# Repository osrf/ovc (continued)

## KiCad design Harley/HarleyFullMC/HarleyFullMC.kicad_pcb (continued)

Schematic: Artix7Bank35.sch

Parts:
C131: 47u; C_0805; Voltage 10; Tolerance 20%
C132, C133: 4.7u; C_0402; Voltage 6.3; Tolerance 10%
C134, C135, C136, C137: 470n; C_0201; Voltage 6.3; Tolerance 10%
C138, C139, C140: 10n; C_0201; Voltage 6.3; Tolerance 10%
U1: xc7a100tcsg324pkg; BGA324C80P18X18_1500X1500X150; Voltage _; Tolerance _

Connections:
+1V0: U1.F8, U1.F10, U1.G7, U1.G9, U1.G11, U1.H8, U1.J7, U1.J11, U1.K8, U1.L7, U1.L11, U1.M8, U1.M10, U1.N7, U1.N9, U1.N11; also elsewhere on the board
+1V8: U1.F12, U1.H12, U1.K12, U1.M12; also elsewhere on the board
+2V5: U1.A17, U1.C13, U1.D16, U1.G15, U1.H18, U1.K4, U1.K14, U1.L17, U1.N3, U1.N13, U1.P6, U1.P8, U1.P11, U1.P12, U1.P13, U1.P16, U1.R9, U1.T2, U1.T12, U1.U5, U1.U15, U1.V8, U1.V18; also elsewhere on the board
+3V3: U1.B10; also elsewhere on the board
/Sheet56A15EBD/GND_ADC: U1.H9, U1.J9, U1.K10; also elsewhere on the board
Artix_FX3_CLK: U1.P3; also elsewhere on the board
CAM_CLK_IN+: U1.B13; also elsewhere on the board
CAM_CLK_IN-: U1.B14; also elsewhere on the board
CAM_CLK_OUT+: U1.F15; also elsewhere on the board
CAM_CLK_OUT-: U1.F16; also elsewhere on the board
CAM_CLK_PLL: U1.C10; also elsewhere on the board
CAM_DOUT0+: U1.A11; also elsewhere on the board
CAM_DOUT0-: U1.B11; also elsewhere on the board
CAM_DOUT1+: U1.A14; also elsewhere on the board
CAM_DOUT1-: U1.A13; also elsewhere on the board
CAM_DOUT2+: U1.A16; also elsewhere on the board
CAM_DOUT2-: U1.A15; also elsewhere on the board
CAM_DOUT3+: U1.B17; also elsewhere on the board
CAM_DOUT3-: U1.B16; also elsewhere on the board
CAM_RST#: U1.B9; also elsewhere on the board
CAM_SS#: U1.A8; also elsewhere on the board
CAM_SYNC+: U1.B18; also elsewhere on the board
CAM_SYNC-: U1.A18; also elsewhere on the board
CAM_monitor0: U1.A10; also elsewhere on the board
CAM_trigger0: U1.D10; also elsewhere on the board
CAM_trigger1: U1.D9; also elsewhere on the board
DDR_A0: U1.G2; also elsewhere on the board
DDR_A1: U1.H5; also elsewhere on the board
DDR_A2: U1.G3; also elsewhere on the board
DDR_A3: U1.H2; also elsewhere on the board
DDR_A4: U1.J4; also elsewhere on the board
DDR_A5: U1.J2; also elsewhere on the board
DDR_A6: U1.G6; also elsewhere on the board
DDR_A7: U1.K1; also elsewhere on the board
DDR_A8: U1.H6; also elsewhere on the board
DDR_A9: U1.J3; also elsewhere on the board
DDR_A10: U1.F6; also elsewhere on the board
DDR_A11: U1.H4; also elsewhere on the board
DDR_A12: U1.G4; also elsewhere on the board
DDR_A13: U1.K2; also elsewhere on the board
DDR_BA0: U1.E1; also elsewhere on the board
DDR_BA1: U1.G1; also elsewhere on the board
DDR_BA2: U1.F1; also elsewhere on the board
DDR_CAS#: U1.C1; also elsewhere on the board
DDR_CKE: U1.H1; also elsewhere on the board
DDR_CLK+: U1.F4; also elsewhere on the board
DDR_CLK-: U1.F3; also elsewhere on the board
DDR_DQL0: U1.B7; also elsewhere on the board
DDR_DQL1: U1.D8; also elsewhere on the board
DDR_DQL2: U1.C7; also elsewhere on the board
DDR_DQL3: U1.B6; also elsewhere on the board
DDR_DQL4: U1.E5; also elsewhere on the board
DDR_DQL5: U1.D7; also elsewhere on the board
DDR_DQL6: U1.E6; also elsewhere on the board
DDR_DQL7: U1.E7; also elsewhere on the board
DDR_DQSL+: U1.A6; also elsewhere on the board
DDR_DQSL-: U1.A5; also elsewhere on the board
DDR_DQSU+: U1.B1; also elsewhere on the board
DDR_DQSU-: U1.A1; also elsewhere on the board
DDR_DQU0: U1.B2; also elsewhere on the board
DDR_DQU1: U1.D4; also elsewhere on the board
DDR_DQU2: U1.B3; also elsewhere on the board
DDR_DQU3: U1.D5; also elsewhere on the board
DDR_DQU4: U1.B4; also elsewhere on the board
DDR_DQU5: U1.C4; also elsewhere on the board
DDR_DQU6: U1.A3; also elsewhere on the board
DDR_DQU7: U1.A4; also elsewhere on the board
DDR_ODT: U1.E2; also elsewhere on the board
DDR_RAS#: U1.C2; also elsewhere on the board
DDR_RST#: U1.J5; also elsewhere on the board
DDR_VDD: C131.1, C132.1, C133.1, C134.1, C135.1, C136.1, C137.1, C138.1, C139.1, C140.1, U1.A7, U1.C3, U1.D6, U1.F2, U1.G5, U1.J1; also elsewhere on the board
DDR_WE#: U1.D2; also elsewhere on the board
FPGADebug1: U1.C16; also elsewhere on the board
FPGADebug2: U1.F14; also elsewhere on the board
FPGA_CLK: U1.N5; also elsewhere on the board
FPGA_JTAG_TCK: U1.E10; also elsewhere on the board
FPGA_JTAG_TDI: U1.E11; also elsewhere on the board
FPGA_JTAG_TDO: U1.E13; also elsewhere on the board
FPGA_JTAG_TMS: U1.E12; also elsewhere on the board
FPGA_LED: U1.C17; also elsewhere on the board
FPGA_SS_CCLK: U1.E9; also elsewhere on the board
FPGA_SS_DIN: U1.K18; also elsewhere on the board
FPGA_SS_DONE: U1.P10; also elsewhere on the board
FPGA_SS_DOUT: U1.T16; also elsewhere on the board
FPGA_SS_INIT_B: U1.P7; also elsewhere on the board
FPGA_SS_PROGRAM_B: U1.P9; also elsewhere on the board
FX3_A0: U1.T9; also elsewhere on the board
FX3_A1: U1.R11; also elsewhere on the board
FX3_DQ0: U1.V7; also elsewhere on the board
FX3_DQ1: U1.R3; also elsewhere on the board
FX3_DQ2: U1.R2; also elsewhere on the board
FX3_DQ3: U1.V4; also elsewhere on the board
FX3_DQ4: U1.T4; also elsewhere on the board
FX3_DQ5: U1.T3; also elsewhere on the board
FX3_DQ6: U1.V9; also elsewhere on the board
FX3_DQ7: U1.U6; also elsewhere on the board
FX3_DQ8: U1.V10; also elsewhere on the board
FX3_DQ9: U1.V11; also elsewhere on the board
FX3_DQ10: U1.U11; also elsewhere on the board
FX3_DQ11: U1.U13; also elsewhere on the board
FX3_DQ12: U1.V12; also elsewhere on the board
FX3_DQ13: U1.V14; also elsewhere on the board
FX3_DQ14: U1.T10; also elsewhere on the board
FX3_DQ15: U1.T5; also elsewhere on the board
FX3_DQ16: U1.U16; also elsewhere on the board
FX3_DQ17: U1.U12; also elsewhere on the board
FX3_DQ18: U1.V17; also elsewhere on the board
FX3_DQ19: U1.T14; also elsewhere on the board
FX3_DQ20: U1.V16; also elsewhere on the board
FX3_DQ21: U1.P14; also elsewhere on the board
FX3_DQ22: U1.R12; also elsewhere on the board
FX3_DQ23: U1.T11; also elsewhere on the board
FX3_DQ24: U1.P5; also elsewhere on the board
FX3_DQ25: U1.T13; also elsewhere on the board
FX3_DQ26: U1.R8; also elsewhere on the board
FX3_DQ27: U1.L14; also elsewhere on the board
FX3_DQ28: U1.U4; also elsewhere on the board
FX3_DQ29: U1.P18; also elsewhere on the board
FX3_DQ30: U1.V1; also elsewhere on the board
FX3_DQ31: U1.R16; also elsewhere on the board
FX3_FLAGA: U1.V6; also elsewhere on the board
FX3_FLAGB: U1.U9; also elsewhere on the board
FX3_FLAGC: U1.T15; also elsewhere on the board
FX3_FLAGD: U1.T8; also elsewhere on the board
FX3_PKT_END#: U1.R5; also elsewhere on the board
FX3_SLCS#: U1.U14; also elsewhere on the board
FX3_SLOE#: U1.R10; also elsewhere on the board
FX3_SLRD#: U1.R6; also elsewhere on the board
FX3_SLWR#: U1.V15; also elsewhere on the board
GND: C131.2, C132.2, C133.2, C134.2, C135.2, C136.2, C137.2, C138.2, C139.2, C140.2, U1.A2, U1.A12, U1.B5, U1.B15, U1.C8, U1.C18, U1.D1, U1.D11, U1.E4, U1.E8, U1.E14, U1.F7, U1.F9, U1.F11, U1.F17, U1.G8, U1.G10, U1.G12, U1.H3, U1.H7, U1.H11, U1.H13, U1.J6, U1.J8, U1.J10, U1.J12, U1.J16, U1.K7, U1.K9, U1.K11, U1.L2, U1.L8, U1.L9, U1.L10, U1.L12, U1.M5, U1.M7, U1.M9, U1.M11, U1.M15, U1.N8, U1.N10, U1.N12, U1.N18, U1.P1, U1.R4, U1.R14, U1.T7, U1.T17, U1.U10, U1.V3, U1.V13; also elsewhere on the board
IMU_SS#: U1.C11; also elsewhere on the board
unnamed 164: U1.H10; also elsewhere on the board
P_LVDS1+: U1.E18; also elsewhere on the board
P_LVDS1-: U1.D18; also elsewhere on the board
P_LVDS2+: U1.G18; also elsewhere on the board
P_LVDS2-: U1.F18; also elsewhere on the board
P_LVDS3+: U1.J17; also elsewhere on the board
P_LVDS3-: U1.J18; also elsewhere on the board
P_LVDS4+: U1.H16; also elsewhere on the board
P_LVDS4-: U1.G16; also elsewhere on the board
P_LVDS5+: U1.H14; also elsewhere on the board
P_LVDS5-: U1.G14; also elsewhere on the board
P_LVDS6+: U1.M18; also elsewhere on the board
P_LVDS6-: U1.L18; also elsewhere on the board
P_LVDS7+: U1.L15; also elsewhere on the board
P_LVDS7-: U1.L16; also elsewhere on the board
P_LVDS8+: U1.N15; also elsewhere on the board
P_LVDS8-: U1.N16; also elsewhere on the board
P_LVDS9+: U1.T18; also elsewhere on the board
P_LVDS9-: U1.R18; also elsewhere on the board
P_LVDS10+: U1.U17; also elsewhere on the board
P_LVDS10-: U1.U18; also elsewhere on the board
P_LVDS11+: U1.D17; also elsewhere on the board
P_LVDS11-: U1.E17; also elsewhere on the board
P_LVDS12+: U1.R17; also elsewhere on the board
P_LVDS12-: U1.P17; also elsewhere on the board
P_LVDS13+: U1.R15; also elsewhere on the board
P_LVDS13-: U1.P15; also elsewhere on the board
P_LVDS14+: U1.M13; also elsewhere on the board
P_LVDS14-: U1.L13; also elsewhere on the board
SPI_MISO: U1.A9; also elsewhere on the board
SPI_MOSI: U1.C9; also elsewhere on the board
SPI_SCK: U1.B8; also elsewhere on the board

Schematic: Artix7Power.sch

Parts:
C103: 330u; C_1210; Voltage 4; Tolerance 20%
C104: 100u; C_1206; Voltage 6.3; Tolerance 20%
C105: 47u; C_0805; Voltage 10; Tolerance 20%
C106, C107, C109, C110, C113, C127, C129: 4.7u; C_0402; Voltage 6.3; Tolerance 10%
C111, C112, C115, C117, C119, C120, C121, C122, C123, C124, C130, C161: 470n; C_0201; Voltage 6.3; Tolerance 10%
U1: xc7a100tcsg324pkg; BGA324C80P18X18_1500X1500X150; Voltage _; Tolerance _

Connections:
+1V0: C103.1, C104.1, C107.1, C110.1, C111.1, C113.1, C120.1, C121.1, C122.1, C123.1, C124.1, C127.1, C129.1, C130.1, C161.1, U1.F8, U1.F10, U1.G7, U1.G9, U1.G11, U1.H8, U1.J7, U1.J11, U1.K8, U1.L7, U1.L11, U1.M8, U1.M10, U1.N7, U1.N9, U1.N11; also elsewhere on the board
+1V8: C105.1, C106.1, C109.1, C112.1, C115.1, C117.1, C119.1, U1.F12, U1.H12, U1.K12, U1.M12; also elsewhere on the board
+2V5: U1.A17, U1.C13, U1.D16, U1.G15, U1.H18, U1.K4, U1.K14, U1.L17, U1.N3, U1.N13, U1.P6, U1.P8, U1.P11, U1.P12, U1.P13, U1.P16, U1.R9, U1.T2, U1.T12, U1.U5, U1.U15, U1.V8, U1.V18; also elsewhere on the board
+3V3: U1.B10; also elsewhere on the board
/Sheet56A15EBD/GND_ADC: U1.H9, U1.J9, U1.K10; also elsewhere on the board
Artix_FX3_CLK: U1.P3; also elsewhere on the board
CAM_CLK_IN+: U1.B13; also elsewhere on the board
CAM_CLK_IN-: U1.B14; also elsewhere on the board
CAM_CLK_OUT+: U1.F15; also elsewhere on the board
CAM_CLK_OUT-: U1.F16; also elsewhere on the board
CAM_CLK_PLL: U1.C10; also elsewhere on the board
CAM_DOUT0+: U1.A11; also elsewhere on the board
CAM_DOUT0-: U1.B11; also elsewhere on the board
CAM_DOUT1+: U1.A14; also elsewhere on the board
CAM_DOUT1-: U1.A13; also elsewhere on the board
CAM_DOUT2+: U1.A16; also elsewhere on the board
CAM_DOUT2-: U1.A15; also elsewhere on the board
CAM_DOUT3+: U1.B17; also elsewhere on the board
CAM_DOUT3-: U1.B16; also elsewhere on the board
CAM_RST#: U1.B9; also elsewhere on the board
CAM_SS#: U1.A8; also elsewhere on the board
CAM_SYNC+: U1.B18; also elsewhere on the board
CAM_SYNC-: U1.A18; also elsewhere on the board
CAM_monitor0: U1.A10; also elsewhere on the board
CAM_trigger0: U1.D10; also elsewhere on the board
CAM_trigger1: U1.D9; also elsewhere on the board
DDR_A0: U1.G2; also elsewhere on the board
DDR_A1: U1.H5; also elsewhere on the board
DDR_A2: U1.G3; also elsewhere on the board
DDR_A3: U1.H2; also elsewhere on the board
DDR_A4: U1.J4; also elsewhere on the board
DDR_A5: U1.J2; also elsewhere on the board
DDR_A6: U1.G6; also elsewhere on the board
DDR_A7: U1.K1; also elsewhere on the board
DDR_A8: U1.H6; also elsewhere on the board
DDR_A9: U1.J3; also elsewhere on the board
DDR_A10: U1.F6; also elsewhere on the board
DDR_A11: U1.H4; also elsewhere on the board
DDR_A12: U1.G4; also elsewhere on the board
DDR_A13: U1.K2; also elsewhere on the board
DDR_BA0: U1.E1; also elsewhere on the board
DDR_BA1: U1.G1; also elsewhere on the board
DDR_BA2: U1.F1; also elsewhere on the board
DDR_CAS#: U1.C1; also elsewhere on the board
DDR_CKE: U1.H1; also elsewhere on the board
DDR_CLK+: U1.F4; also elsewhere on the board
DDR_CLK-: U1.F3; also elsewhere on the board
DDR_DQL0: U1.B7; also elsewhere on the board
DDR_DQL1: U1.D8; also elsewhere on the board
DDR_DQL2: U1.C7; also elsewhere on the board
DDR_DQL3: U1.B6; also elsewhere on the board
DDR_DQL4: U1.E5; also elsewhere on the board
DDR_DQL5: U1.D7; also elsewhere on the board
DDR_DQL6: U1.E6; also elsewhere on the board
DDR_DQL7: U1.E7; also elsewhere on the board
DDR_DQSL+: U1.A6; also elsewhere on the board
DDR_DQSL-: U1.A5; also elsewhere on the board
DDR_DQSU+: U1.B1; also elsewhere on the board
DDR_DQSU-: U1.A1; also elsewhere on the board
DDR_DQU0: U1.B2; also elsewhere on the board
DDR_DQU1: U1.D4; also elsewhere on the board
DDR_DQU2: U1.B3; also elsewhere on the board
DDR_DQU3: U1.D5; also elsewhere on the board
DDR_DQU4: U1.B4; also elsewhere on the board
DDR_DQU5: U1.C4; also elsewhere on the board
DDR_DQU6: U1.A3; also elsewhere on the board
DDR_DQU7: U1.A4; also elsewhere on the board
DDR_ODT: U1.E2; also elsewhere on the board
DDR_RAS#: U1.C2; also elsewhere on the board
DDR_RST#: U1.J5; also elsewhere on the board
DDR_VDD: U1.A7, U1.C3, U1.D6, U1.F2, U1.G5, U1.J1; also elsewhere on the board
DDR_WE#: U1.D2; also elsewhere on the board
FPGADebug1: U1.C16; also elsewhere on the board
FPGADebug2: U1.F14; also elsewhere on the board
FPGA_CLK: U1.N5; also elsewhere on the board
FPGA_JTAG_TCK: U1.E10; also elsewhere on the board
FPGA_JTAG_TDI: U1.E11; also elsewhere on the board
FPGA_JTAG_TDO: U1.E13; also elsewhere on the board
FPGA_JTAG_TMS: U1.E12; also elsewhere on the board
FPGA_LED: U1.C17; also elsewhere on the board
FPGA_SS_CCLK: U1.E9; also elsewhere on the board
FPGA_SS_DIN: U1.K18; also elsewhere on the board
FPGA_SS_DONE: U1.P10; also elsewhere on the board
FPGA_SS_DOUT: U1.T16; also elsewhere on the board
FPGA_SS_INIT_B: U1.P7; also elsewhere on the board
FPGA_SS_PROGRAM_B: U1.P9; also elsewhere on the board
FX3_A0: U1.T9; also elsewhere on the board
FX3_A1: U1.R11; also elsewhere on the board
FX3_DQ0: U1.V7; also elsewhere on the board
FX3_DQ1: U1.R3; also elsewhere on the board
FX3_DQ2: U1.R2; also elsewhere on the board
FX3_DQ3: U1.V4; also elsewhere on the board
FX3_DQ4: U1.T4; also elsewhere on the board
FX3_DQ5: U1.T3; also elsewhere on the board
FX3_DQ6: U1.V9; also elsewhere on the board
FX3_DQ7: U1.U6; also elsewhere on the board
FX3_DQ8: U1.V10; also elsewhere on the board
FX3_DQ9: U1.V11; also elsewhere on the board
FX3_DQ10: U1.U11; also elsewhere on the board
FX3_DQ11: U1.U13; also elsewhere on the board
FX3_DQ12: U1.V12; also elsewhere on the board
FX3_DQ13: U1.V14; also elsewhere on the board
FX3_DQ14: U1.T10; also elsewhere on the board
FX3_DQ15: U1.T5; also elsewhere on the board
FX3_DQ16: U1.U16; also elsewhere on the board
FX3_DQ17: U1.U12; also elsewhere on the board
FX3_DQ18: U1.V17; also elsewhere on the board
FX3_DQ19: U1.T14; also elsewhere on the board
FX3_DQ20: U1.V16; also elsewhere on the board
FX3_DQ21: U1.P14; also elsewhere on the board
FX3_DQ22: U1.R12; also elsewhere on the board
FX3_DQ23: U1.T11; also elsewhere on the board
FX3_DQ24: U1.P5; also elsewhere on the board
FX3_DQ25: U1.T13; also elsewhere on the board
FX3_DQ26: U1.R8; also elsewhere on the board
FX3_DQ27: U1.L14; also elsewhere on the board
FX3_DQ28: U1.U4; also elsewhere on the board
FX3_DQ29: U1.P18; also elsewhere on the board
FX3_DQ30: U1.V1; also elsewhere on the board
FX3_DQ31: U1.R16; also elsewhere on the board
FX3_FLAGA: U1.V6; also elsewhere on the board
FX3_FLAGB: U1.U9; also elsewhere on the board
FX3_FLAGC: U1.T15; also elsewhere on the board
FX3_FLAGD: U1.T8; also elsewhere on the board
FX3_PKT_END#: U1.R5; also elsewhere on the board
FX3_SLCS#: U1.U14; also elsewhere on the board
FX3_SLOE#: U1.R10; also elsewhere on the board
FX3_SLRD#: U1.R6; also elsewhere on the board
FX3_SLWR#: U1.V15; also elsewhere on the board
GND: C103.2, C104.2, C105.2, C106.2, C107.2, C109.2, C110.2, C111.2, C112.2, C113.2, C115.2, C117.2, C119.2, C120.2, C121.2, C122.2, C123.2, C124.2, C127.2, C129.2, C130.2, C161.2, U1.A2, U1.A12, U1.B5, U1.B15, U1.C8, U1.C18, U1.D1, U1.D11, U1.E4, U1.E8, U1.E14, U1.F7, U1.F9, U1.F11, U1.F17, U1.G8, U1.G10, U1.G12, U1.H3, U1.H7, U1.H11, U1.H13, U1.J6, U1.J8, U1.J10, U1.J12, U1.J16, U1.K7, U1.K9, U1.K11, U1.L2, U1.L8, U1.L9, U1.L10, U1.L12, U1.M5, U1.M7, U1.M9, U1.M11, U1.M15, U1.N8, U1.N10, U1.N12, U1.N18, U1.P1, U1.R4, U1.R14, U1.T7, U1.T17, U1.U10, U1.V3, U1.V13; also elsewhere on the board
IMU_SS#: U1.C11; also elsewhere on the board
unnamed 164: U1.H10; also elsewhere on the board
P_LVDS1+: U1.E18; also elsewhere on the board
P_LVDS1-: U1.D18; also elsewhere on the board
P_LVDS2+: U1.G18; also elsewhere on the board
P_LVDS2-: U1.F18; also elsewhere on the board
P_LVDS3+: U1.J17; also elsewhere on the board
P_LVDS3-: U1.J18; also elsewhere on the board
P_LVDS4+: U1.H16; also elsewhere on the board
P_LVDS4-: U1.G16; also elsewhere on the board
P_LVDS5+: U1.H14; also elsewhere on the board
P_LVDS5-: U1.G14; also elsewhere on the board
P_LVDS6+: U1.M18; also elsewhere on the board
P_LVDS6-: U1.L18; also elsewhere on the board
P_LVDS7+: U1.L15; also elsewhere on the board
P_LVDS7-: U1.L16; also elsewhere on the board
P_LVDS8+: U1.N15; also elsewhere on the board
P_LVDS8-: U1.N16; also elsewhere on the board
P_LVDS9+: U1.T18; also elsewhere on the board
P_LVDS9-: U1.R18; also elsewhere on the board
P_LVDS10+: U1.U17; also elsewhere on the board
P_LVDS10-: U1.U18; also elsewhere on the board
P_LVDS11+: U1.D17; also elsewhere on the board
P_LVDS11-: U1.E17; also elsewhere on the board
P_LVDS12+: U1.R17; also elsewhere on the board
P_LVDS12-: U1.P17; also elsewhere on the board
P_LVDS13+: U1.R15; also elsewhere on the board
P_LVDS13-: U1.P15; also elsewhere on the board
P_LVDS14+: U1.M13; also elsewhere on the board
P_LVDS14-: U1.L13; also elsewhere on the board
SPI_MISO: U1.A9; also elsewhere on the board
SPI_MOSI: U1.C9; also elsewhere on the board
SPI_SCK: U1.B8; also elsewhere on the board

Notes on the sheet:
VCCINT
VCCBRAM
VCCAUX
Additional Decoupling for XC7A100T

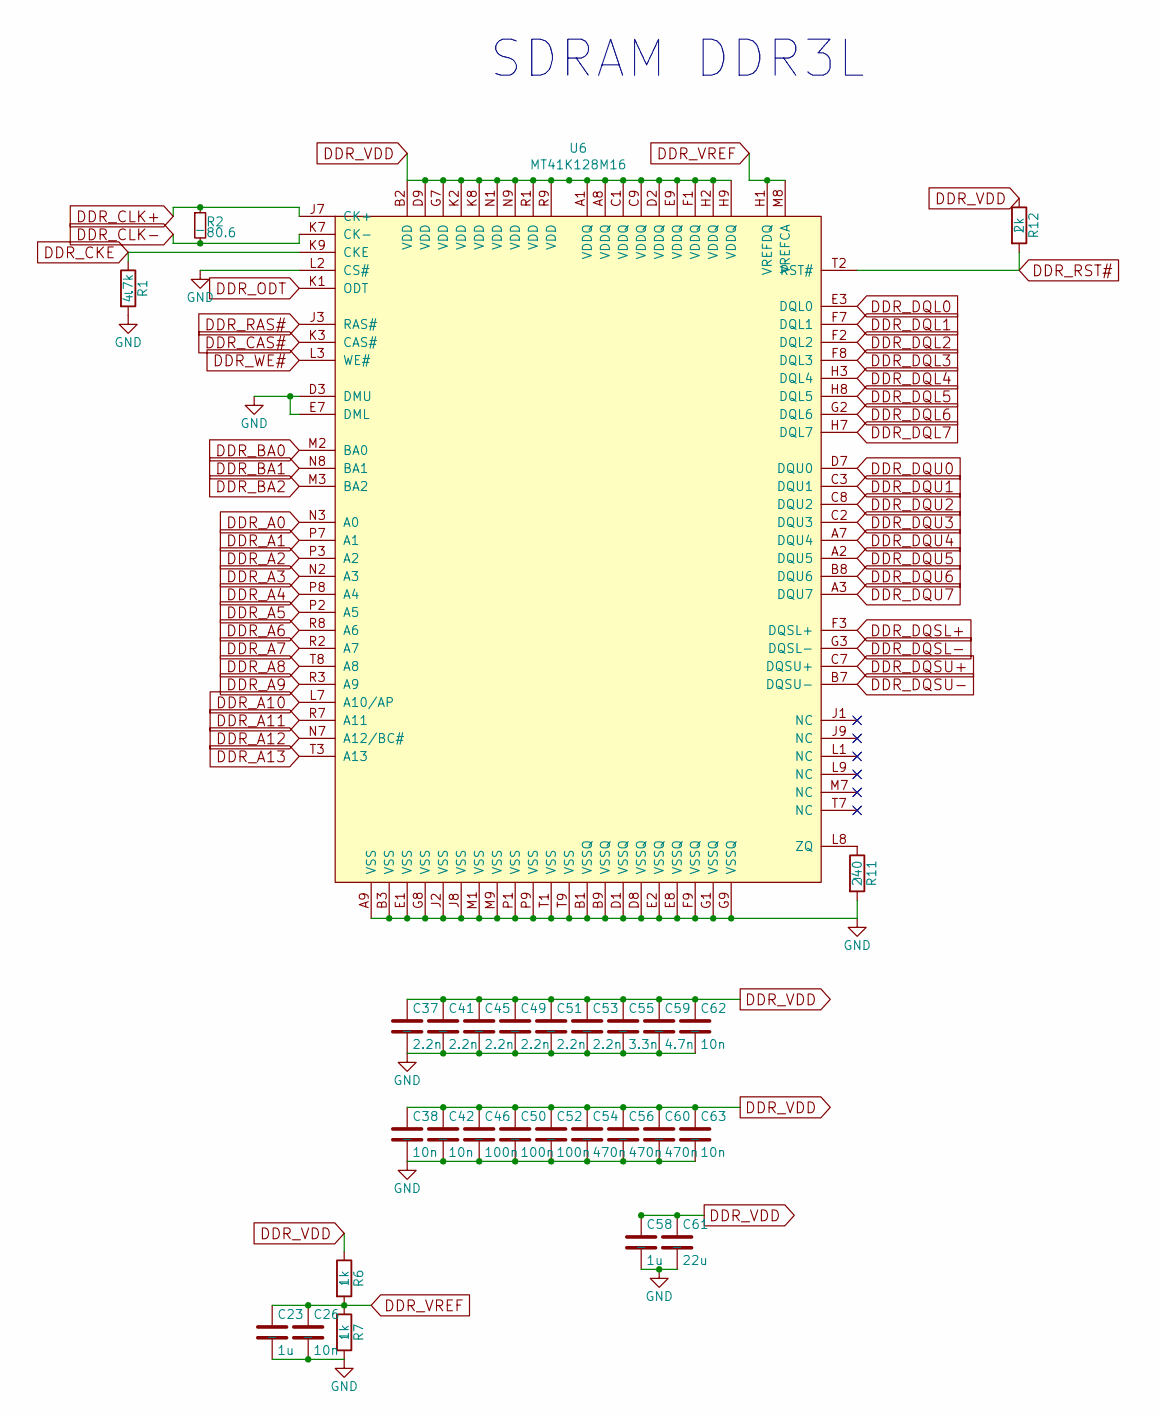
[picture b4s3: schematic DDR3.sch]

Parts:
C23, C58: 1u; C_0201; Voltage 6.3; Tolerance 20%
C26, C38, C42, C62, C63: 10n; C_0201; Voltage 10; Tolerance 10%
C37, C41, C45, C49, C51, C53: 2.2n; C_0201; Voltage 25; Tolerance 10%
C46, C50, C52: 100n; C_0201; Voltage 6.3; Tolerance 10%
C54, C56, C60: 470n; C_0201; Voltage 6.3; Tolerance 10%
C55: 3.3n; C_0201; Voltage 25; Tolerance 10%
C59: 4.7n; C_0201; Voltage 16; Tolerance 10%
C61: 22u; C_0805; Voltage 6.3; Tolerance 10%
R1: 4.7k; C_0201; Voltage _; Tolerance 1%
R2: 80.6; C_0201; Voltage _; Tolerance 1%
R6, R7: 1k; C_0201; Voltage _; Tolerance 1%
R11: 240; C_0201; Voltage _; Tolerance 1%
R12: 2k; C_0201; Voltage _; Tolerance 1%
U6: MT41K128M16; WBGA96C80P6X16_80X1400X110; Voltage _; Tolerance _

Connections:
DDR_A0: U6.N3 (A0); also elsewhere on the board
DDR_A1: U6.P7 (A1); also elsewhere on the board
DDR_A2: U6.P3 (A2); also elsewhere on the board
DDR_A3: U6.N2 (A3); also elsewhere on the board
DDR_A4: U6.P8 (A4); also elsewhere on the board
DDR_A5: U6.P2 (A5); also elsewhere on the board
DDR_A6: U6.R8 (A6); also elsewhere on the board
DDR_A7: U6.R2 (A7); also elsewhere on the board
DDR_A8: U6.T8 (A8); also elsewhere on the board
DDR_A9: U6.R3 (A9); also elsewhere on the board
DDR_A10: U6.L7 (A10/AP); also elsewhere on the board
DDR_A11: U6.R7 (A11); also elsewhere on the board
DDR_A12: U6.N7 (A12/BC#); also elsewhere on the board
DDR_A13: U6.T3 (A13); also elsewhere on the board
DDR_BA0: U6.M2 (BA0); also elsewhere on the board
DDR_BA1: U6.N8 (BA1); also elsewhere on the board
DDR_BA2: U6.M3 (BA2); also elsewhere on the board
DDR_CAS#: U6.K3 (CAS#); also elsewhere on the board
DDR_CKE: R1.1, U6.K9 (CKE); also elsewhere on the board
DDR_CLK+: R2.1, U6.J7 (CK+); also elsewhere on the board
DDR_CLK-: R2.2, U6.K7 (CK-); also elsewhere on the board
DDR_DQL0: U6.E3 (DQL0); also elsewhere on the board
DDR_DQL1: U6.F7 (DQL1); also elsewhere on the board
DDR_DQL2: U6.F2 (DQL2); also elsewhere on the board
DDR_DQL3: U6.F8 (DQL3); also elsewhere on the board
DDR_DQL4: U6.H3 (DQL4); also elsewhere on the board
DDR_DQL5: U6.H8 (DQL5); also elsewhere on the board
DDR_DQL6: U6.G2 (DQL6); also elsewhere on the board
DDR_DQL7: U6.H7 (DQL7); also elsewhere on the board
DDR_DQSL+: U6.F3 (DQSL+); also elsewhere on the board
DDR_DQSL-: U6.G3 (DQSL-); also elsewhere on the board
DDR_DQSU+: U6.C7 (DQSU+); also elsewhere on the board
DDR_DQSU-: U6.B7 (DQSU-); also elsewhere on the board
DDR_DQU0: U6.D7 (DQU0); also elsewhere on the board
DDR_DQU1: U6.C3 (DQU1); also elsewhere on the board
DDR_DQU2: U6.C8 (DQU2); also elsewhere on the board
DDR_DQU3: U6.C2 (DQU3); also elsewhere on the board
DDR_DQU4: U6.A7 (DQU4); also elsewhere on the board
DDR_DQU5: U6.A2 (DQU5); also elsewhere on the board
DDR_DQU6: U6.B8 (DQU6); also elsewhere on the board
DDR_DQU7: U6.A3 (DQU7); also elsewhere on the board
DDR_ODT: U6.K1 (ODT); also elsewhere on the board
DDR_RAS#: U6.J3 (RAS#); also elsewhere on the board
DDR_RST#: R12.2, U6.T2 (RST#); also elsewhere on the board
DDR_VDD: C37.1, C38.1, C41.1, C42.1, C45.1, C46.1, C49.1, C50.1, C51.1, C52.1, C53.1, C54.1, C55.1, C56.1, C58.1, C59.1, C60.1, C61.1, C62.1, C63.1, R6.1, R12.1, U6.A1 (VDDQ), U6.A8 (VDDQ), U6.B2 (VDD), U6.C1 (VDDQ), U6.C9 (VDDQ), U6.D2 (VDDQ), U6.D9 (VDD), U6.E9 (VDDQ), U6.F1 (VDDQ), U6.G7 (VDD), U6.H2 (VDDQ), U6.H9 (VDDQ), U6.K2 (VDD), U6.K8 (VDD), U6.N1 (VDD), U6.N9 (VDD), U6.R1 (VDD), U6.R9 (VDD); also elsewhere on the board
DDR_VREF: C23.1, C26.1, R6.2, R7.1, U6.H1 (VREFDQ), U6.M8 (VREFCA)
DDR_WE#: U6.L3 (WE#); also elsewhere on the board
GND: C23.2, C26.2, C37.2, C38.2, C41.2, C42.2, C45.2, C46.2, C49.2, C50.2, C51.2, C52.2, C53.2, C54.2, C55.2, C56.2, C58.2, C59.2, C60.2, C61.2, C62.2, C63.2, R1.2, R7.2, R11.2, U6.A9 (VSS), U6.B1 (VSSQ), U6.B3 (VSS), U6.B9 (VSSQ), U6.D1 (VSSQ), U6.D3 (DMU), U6.D8 (VSSQ), U6.E1 (VSS), U6.E2 (VSSQ), U6.E7 (DML), U6.E8 (VSSQ), U6.F9 (VSSQ), U6.G1 (VSSQ), U6.G8 (VSS), U6.G9 (VSSQ), U6.J2 (VSS), U6.J8 (VSS), U6.L2 (CS#), U6.M1 (VSS), U6.M9 (VSS), U6.P1 (VSS), U6.P9 (VSS), U6.T1 (VSS), U6.T9 (VSS); also elsewhere on the board
unnamed: R11.1, U6.L8 (ZQ)

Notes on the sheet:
SDRAM DDR3L

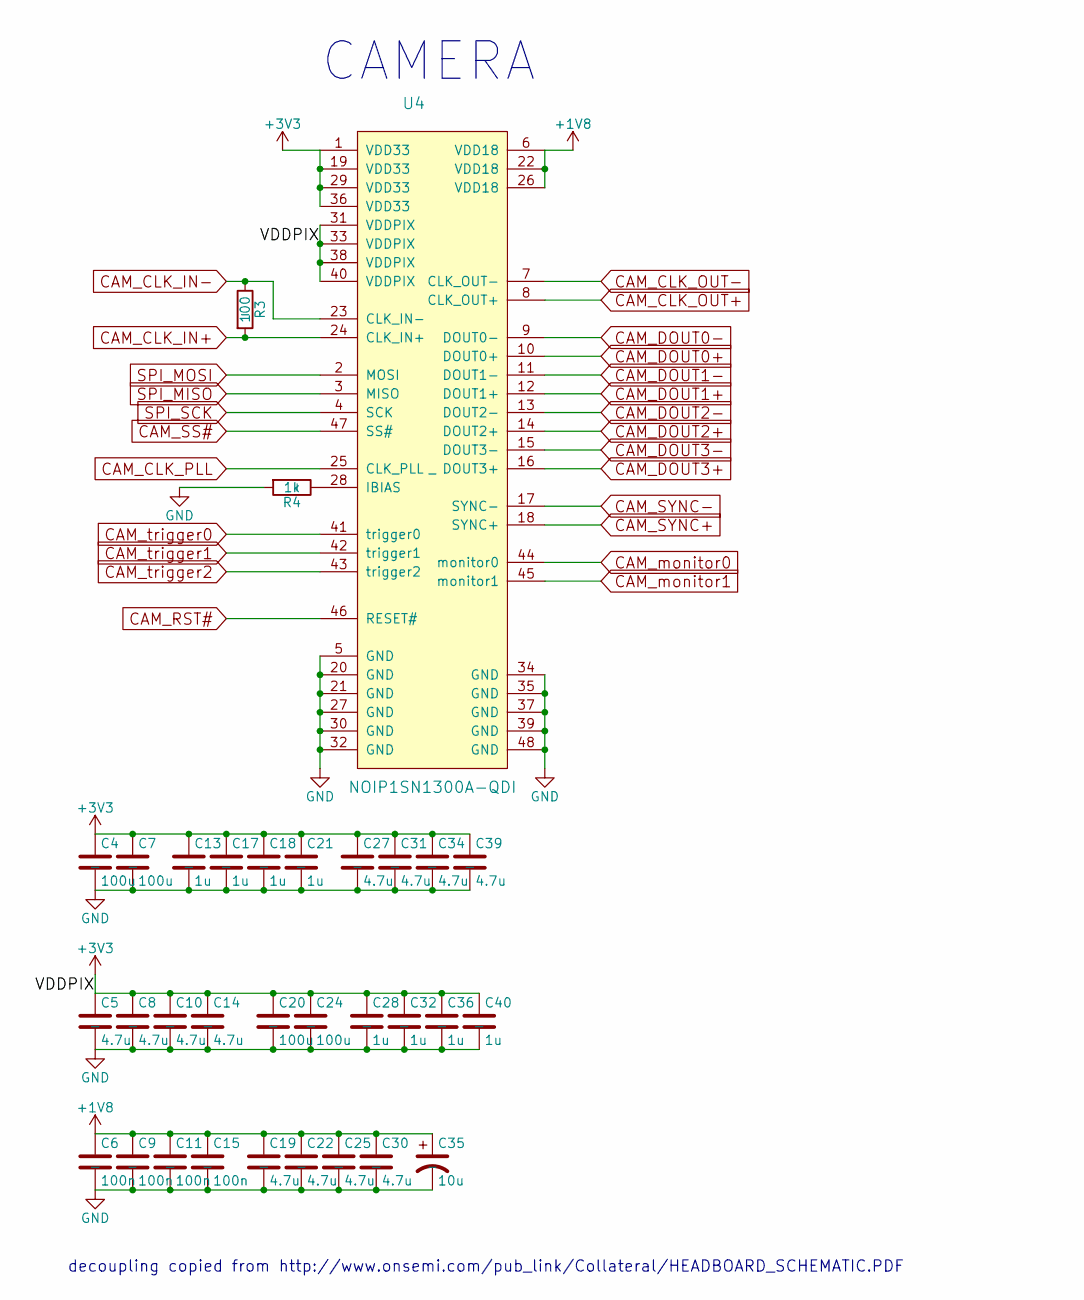
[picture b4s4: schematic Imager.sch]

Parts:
C4, C7, C20, C24: 100u; C_1210; Voltage 10; Tolerance 20%
C5, C8, C10, C14, C19, C22, C25, C27, C30, C31, C34, C39: 4.7u; C_0402; Voltage 6.3; Tolerance 10%
C6, C9, C11, C15: 100n; C_0201; Voltage 6.3; Tolerance 10%
C13, C17, C18, C21, C28, C32, C36, C40: 1u; C_0201; Voltage 16; Tolerance 10%
C35: 10u; C_1206; Voltage 16; Tolerance 20%
R3: 100; C_0201; Voltage _; Tolerance 1%
R4: 1k; R_0402; Voltage _; Tolerance 1%
U4: NOIP1SN1300A-QDI; LCC101.6P1422X1422X165-48; Voltage _; Tolerance _

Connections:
+1V8: C6.1, C9.1, C11.1, C15.1, C19.1, C22.1, C25.1, C30.1, C35.1, U4.6 (VDD18), U4.22 (VDD18), U4.26 (VDD18); also elsewhere on the board
+3V3: C4.1, C5.1, C7.1, C8.1, C10.1, C13.1, C14.1, C17.1, C18.1, C20.1, C21.1, C24.1, C27.1, C28.1, C31.1, C32.1, C34.1, C36.1, C39.1, C40.1, U4.1 (VDD33), U4.19 (VDD33), U4.29 (VDD33), U4.31 (VDDPIX), U4.33 (VDDPIX), U4.36 (VDD33), U4.38 (VDDPIX), U4.40 (VDDPIX); also elsewhere on the board
CAM_CLK_IN+: R3.2, U4.24 (CLK_IN+); also elsewhere on the board
CAM_CLK_IN-: R3.1, U4.23 (CLK_IN-); also elsewhere on the board
CAM_CLK_OUT+: U4.8 (CLK_OUT+); also elsewhere on the board
CAM_CLK_OUT-: U4.7 (CLK_OUT-); also elsewhere on the board
CAM_CLK_PLL: U4.25 (CLK_PLL); also elsewhere on the board
CAM_DOUT0+: U4.10 (DOUT0+); also elsewhere on the board
CAM_DOUT0-: U4.9 (DOUT0-); also elsewhere on the board
CAM_DOUT1+: U4.12 (DOUT1+); also elsewhere on the board
CAM_DOUT1-: U4.11 (DOUT1-); also elsewhere on the board
CAM_DOUT2+: U4.14 (DOUT2+); also elsewhere on the board
CAM_DOUT2-: U4.13 (DOUT2-); also elsewhere on the board
CAM_DOUT3+: U4.16 (DOUT3+); also elsewhere on the board
CAM_DOUT3-: U4.15 (DOUT3-); also elsewhere on the board
CAM_RST#: U4.46 (RESET#); also elsewhere on the board
CAM_SS#: U4.47 (SS#); also elsewhere on the board
CAM_SYNC+: U4.18 (SYNC+); also elsewhere on the board
CAM_SYNC-: U4.17 (SYNC-); also elsewhere on the board
CAM_monitor0: U4.44 (monitor0); also elsewhere on the board
CAM_monitor1: U4.45 (monitor1); also elsewhere on the board
CAM_trigger0: U4.41 (trigger0); also elsewhere on the board
CAM_trigger1: U4.42 (trigger1); also elsewhere on the board
CAM_trigger2: U4.43 (trigger2)
GND: C4.2, C5.2, C6.2, C7.2, C8.2, C9.2, C10.2, C11.2, C13.2, C14.2, C15.2, C17.2, C18.2, C19.2, C20.2, C21.2, C22.2, C24.2, C25.2, C27.2, C28.2, C30.2, C31.2, C32.2, C34.2, C35.2, C36.2, C39.2, C40.2, R4.2, U4.5 (GND), U4.20 (GND), U4.21 (GND), U4.27 (GND), U4.30 (GND), U4.32 (GND), U4.34 (GND), U4.35 (GND), U4.37 (GND), U4.39 (GND), U4.48 (GND); also elsewhere on the board
unnamed: R4.1, U4.28 (IBIAS)
SPI_MISO: U4.3 (MISO); also elsewhere on the board
SPI_MOSI: U4.2 (MOSI); also elsewhere on the board
SPI_SCK: U4.4 (SCK); also elsewhere on the board

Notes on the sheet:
CAMERA
decoupling copied from http://www.onsemi.com/pub_link/Collateral/HEADBOARD_SCHEMATIC.PDF

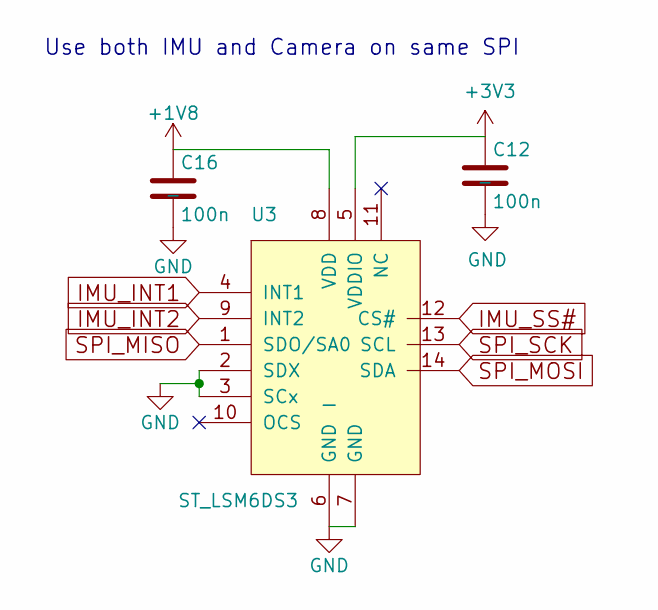
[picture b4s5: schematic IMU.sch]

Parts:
C12, C16: 100n; C_0402; Voltage 6.3; Tolerance 10%
U3: ST_LSM6DS3; LGA14_2.5X3X0.86; Voltage _; Tolerance _

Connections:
+1V8: C16.1, U3.8 (VDD); also elsewhere on the board
+3V3: C12.1, U3.5 (VDDIO); also elsewhere on the board
GND: C12.2, C16.2, U3.2 (SDX), U3.3 (SCx), U3.6 (GND), U3.7 (GND); also elsewhere on the board
IMU_INT1: U3.4 (INT1); also elsewhere on the board
IMU_INT2: U3.9 (INT2)
IMU_SS#: U3.12 (CS#); also elsewhere on the board
SPI_MISO: U3.1 (SDO/SA0); also elsewhere on the board
SPI_MOSI: U3.14 (SDA); also elsewhere on the board
SPI_SCK: U3.13 (SCL); also elsewhere on the board

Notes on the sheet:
Use both IMU and Camera on same SPI

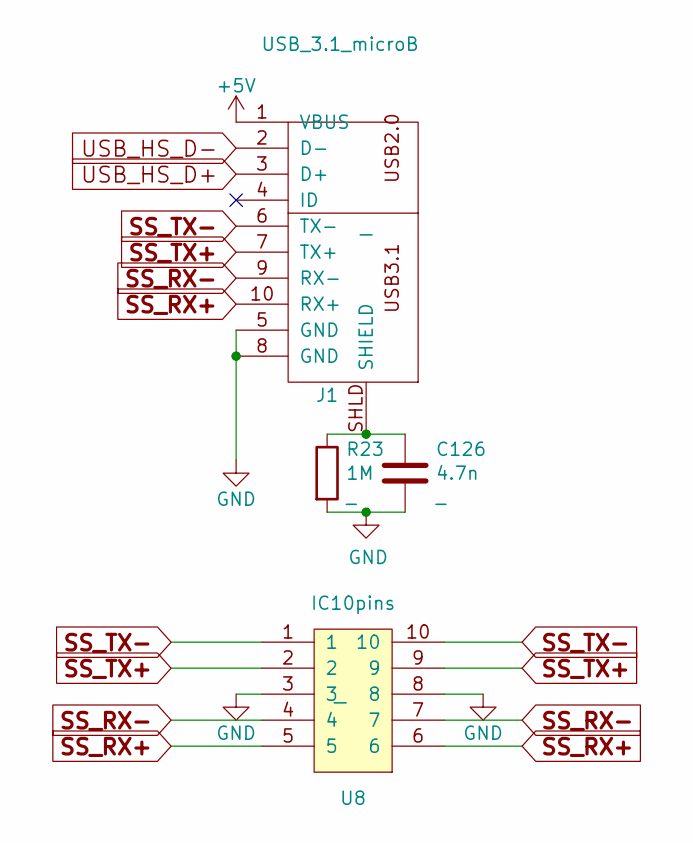
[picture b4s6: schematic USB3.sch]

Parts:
C126: 4.7n; C_0402; Voltage 100; Tolerance 10%
J1: USB_3.1_microB; USB3_Micro-B; Voltage _; Tolerance _
R23: 1M; C_0201; Voltage _; Tolerance 1%
U8: IC10pins; 10-UFDFN; Voltage _; Tolerance _

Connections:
+5V: J1.1 (VBUS); also elsewhere on the board
GND: C126.2, J1.5 (GND), J1.8 (GND), R23.2, U8.3, U8.8; also elsewhere on the board
unnamed: C126.1, J1.SHLD (SHIELD), R23.1
SS_RX+: J1.10 (RX+), U8.5, U8.6; also elsewhere on the board
SS_RX-: J1.9 (RX-), U8.4, U8.7; also elsewhere on the board
SS_TX+: J1.7 (TX+), U8.2, U8.9; also elsewhere on the board
SS_TX-: J1.6 (TX-), U8.1, U8.10; also elsewhere on the board
USB_HS_D+: J1.3 (D+); also elsewhere on the board
USB_HS_D-: J1.2 (D-); also elsewhere on the board

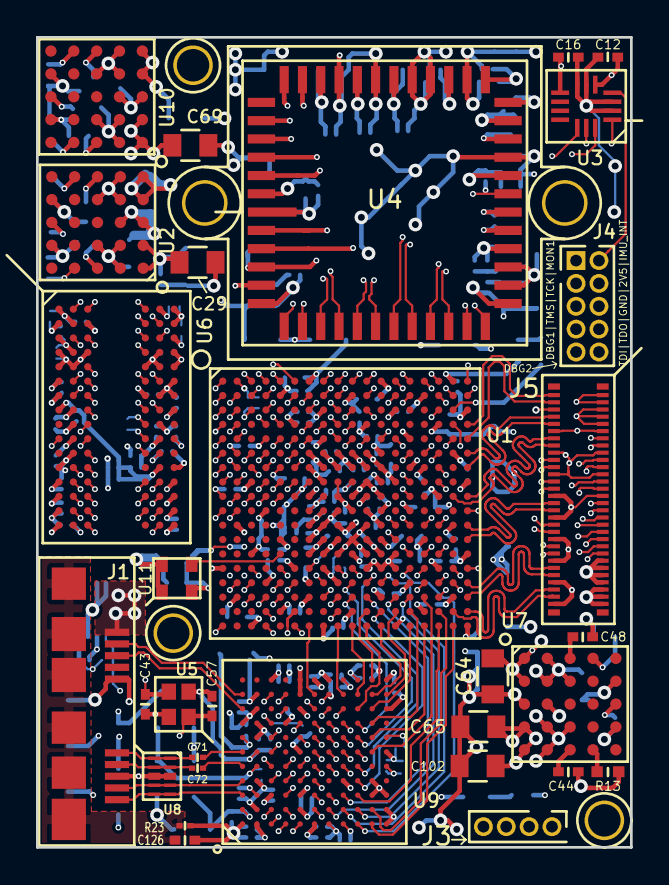
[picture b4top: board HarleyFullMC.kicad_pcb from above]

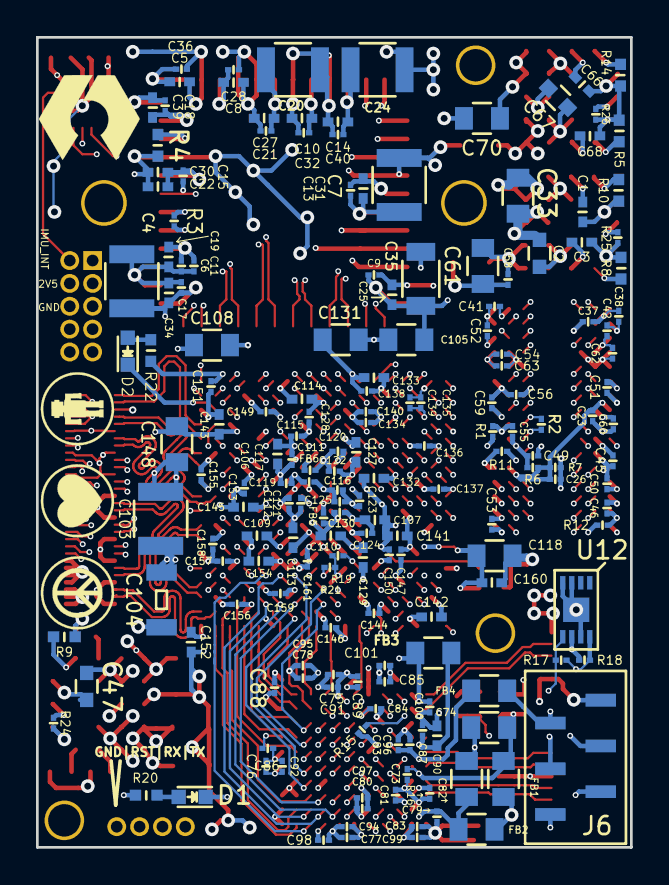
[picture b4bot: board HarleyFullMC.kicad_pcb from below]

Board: 10 copper layers, 33.0 x 45.0 mm, 212 parts (181 on the bottom side), 214 nets.
